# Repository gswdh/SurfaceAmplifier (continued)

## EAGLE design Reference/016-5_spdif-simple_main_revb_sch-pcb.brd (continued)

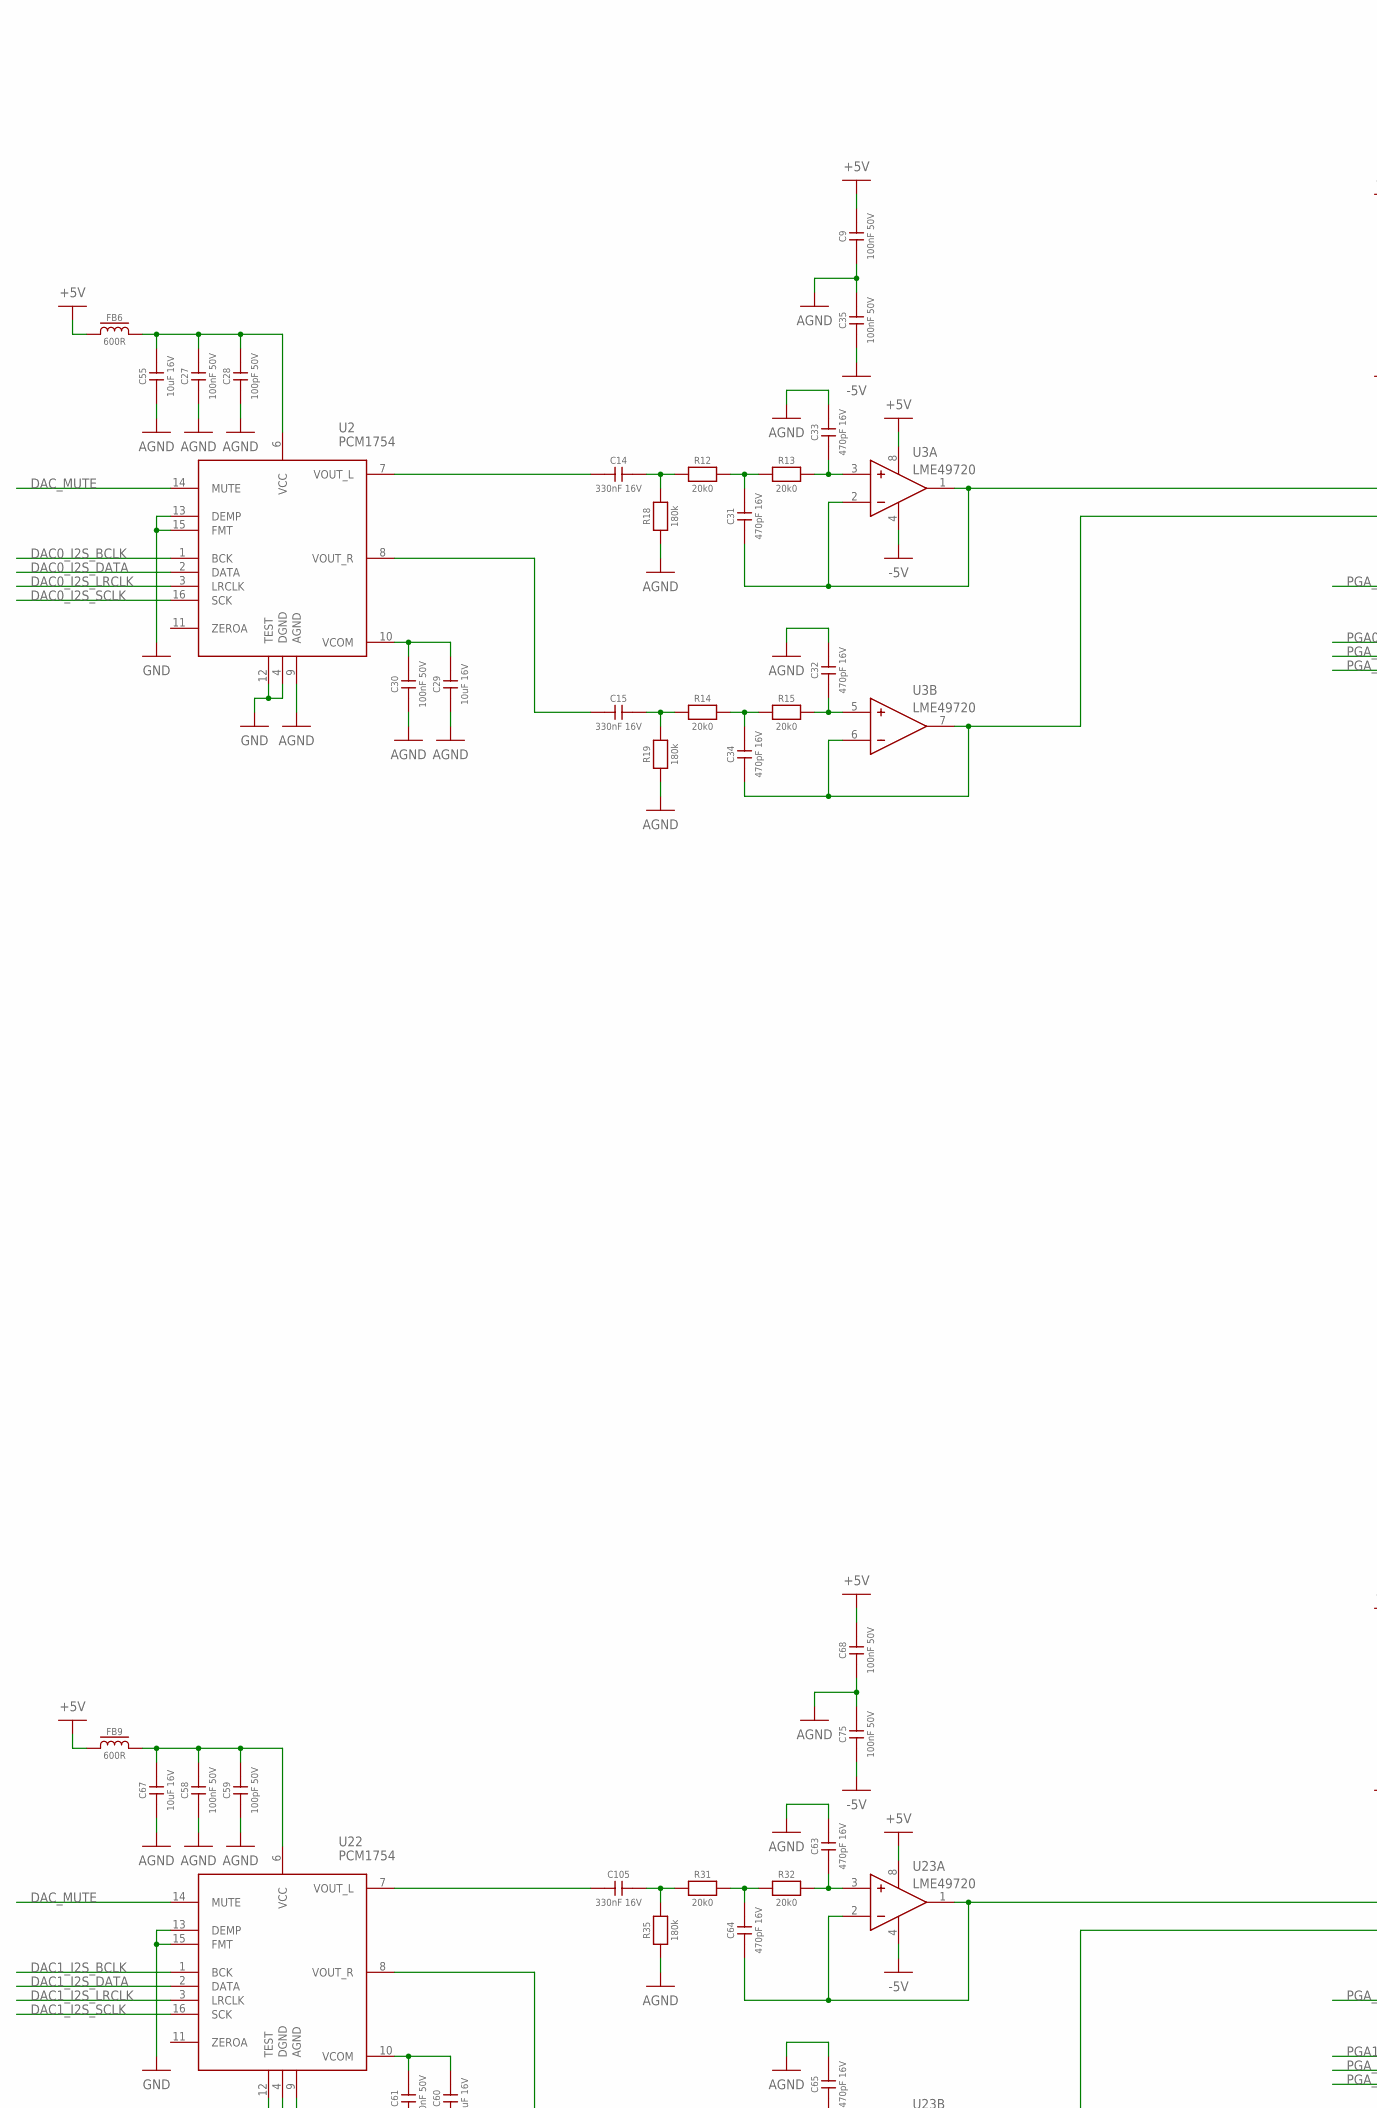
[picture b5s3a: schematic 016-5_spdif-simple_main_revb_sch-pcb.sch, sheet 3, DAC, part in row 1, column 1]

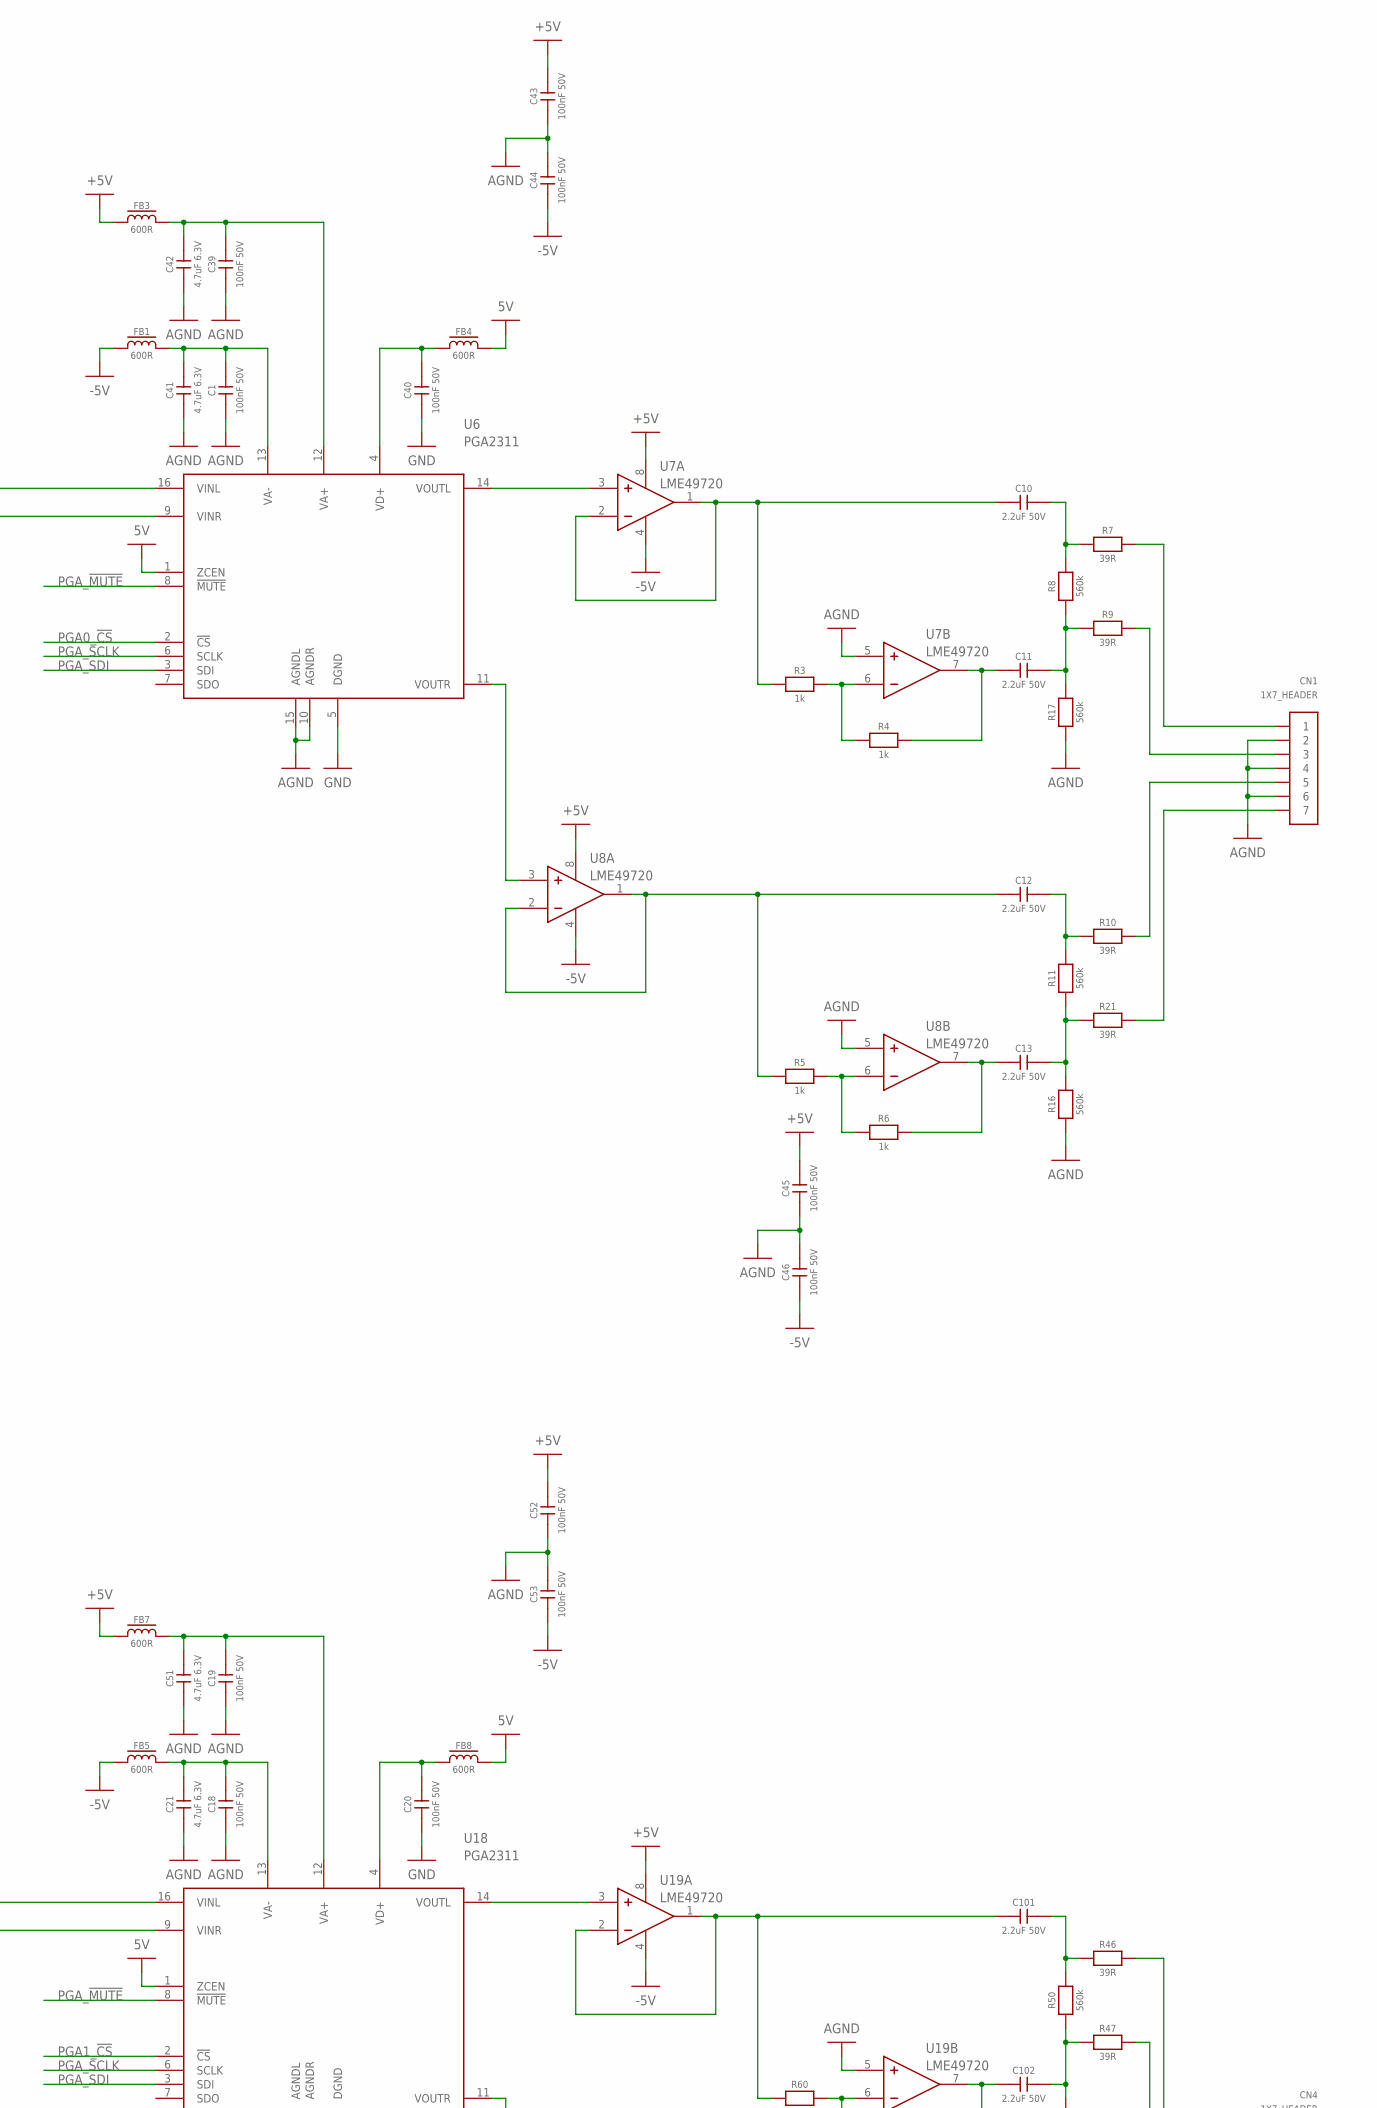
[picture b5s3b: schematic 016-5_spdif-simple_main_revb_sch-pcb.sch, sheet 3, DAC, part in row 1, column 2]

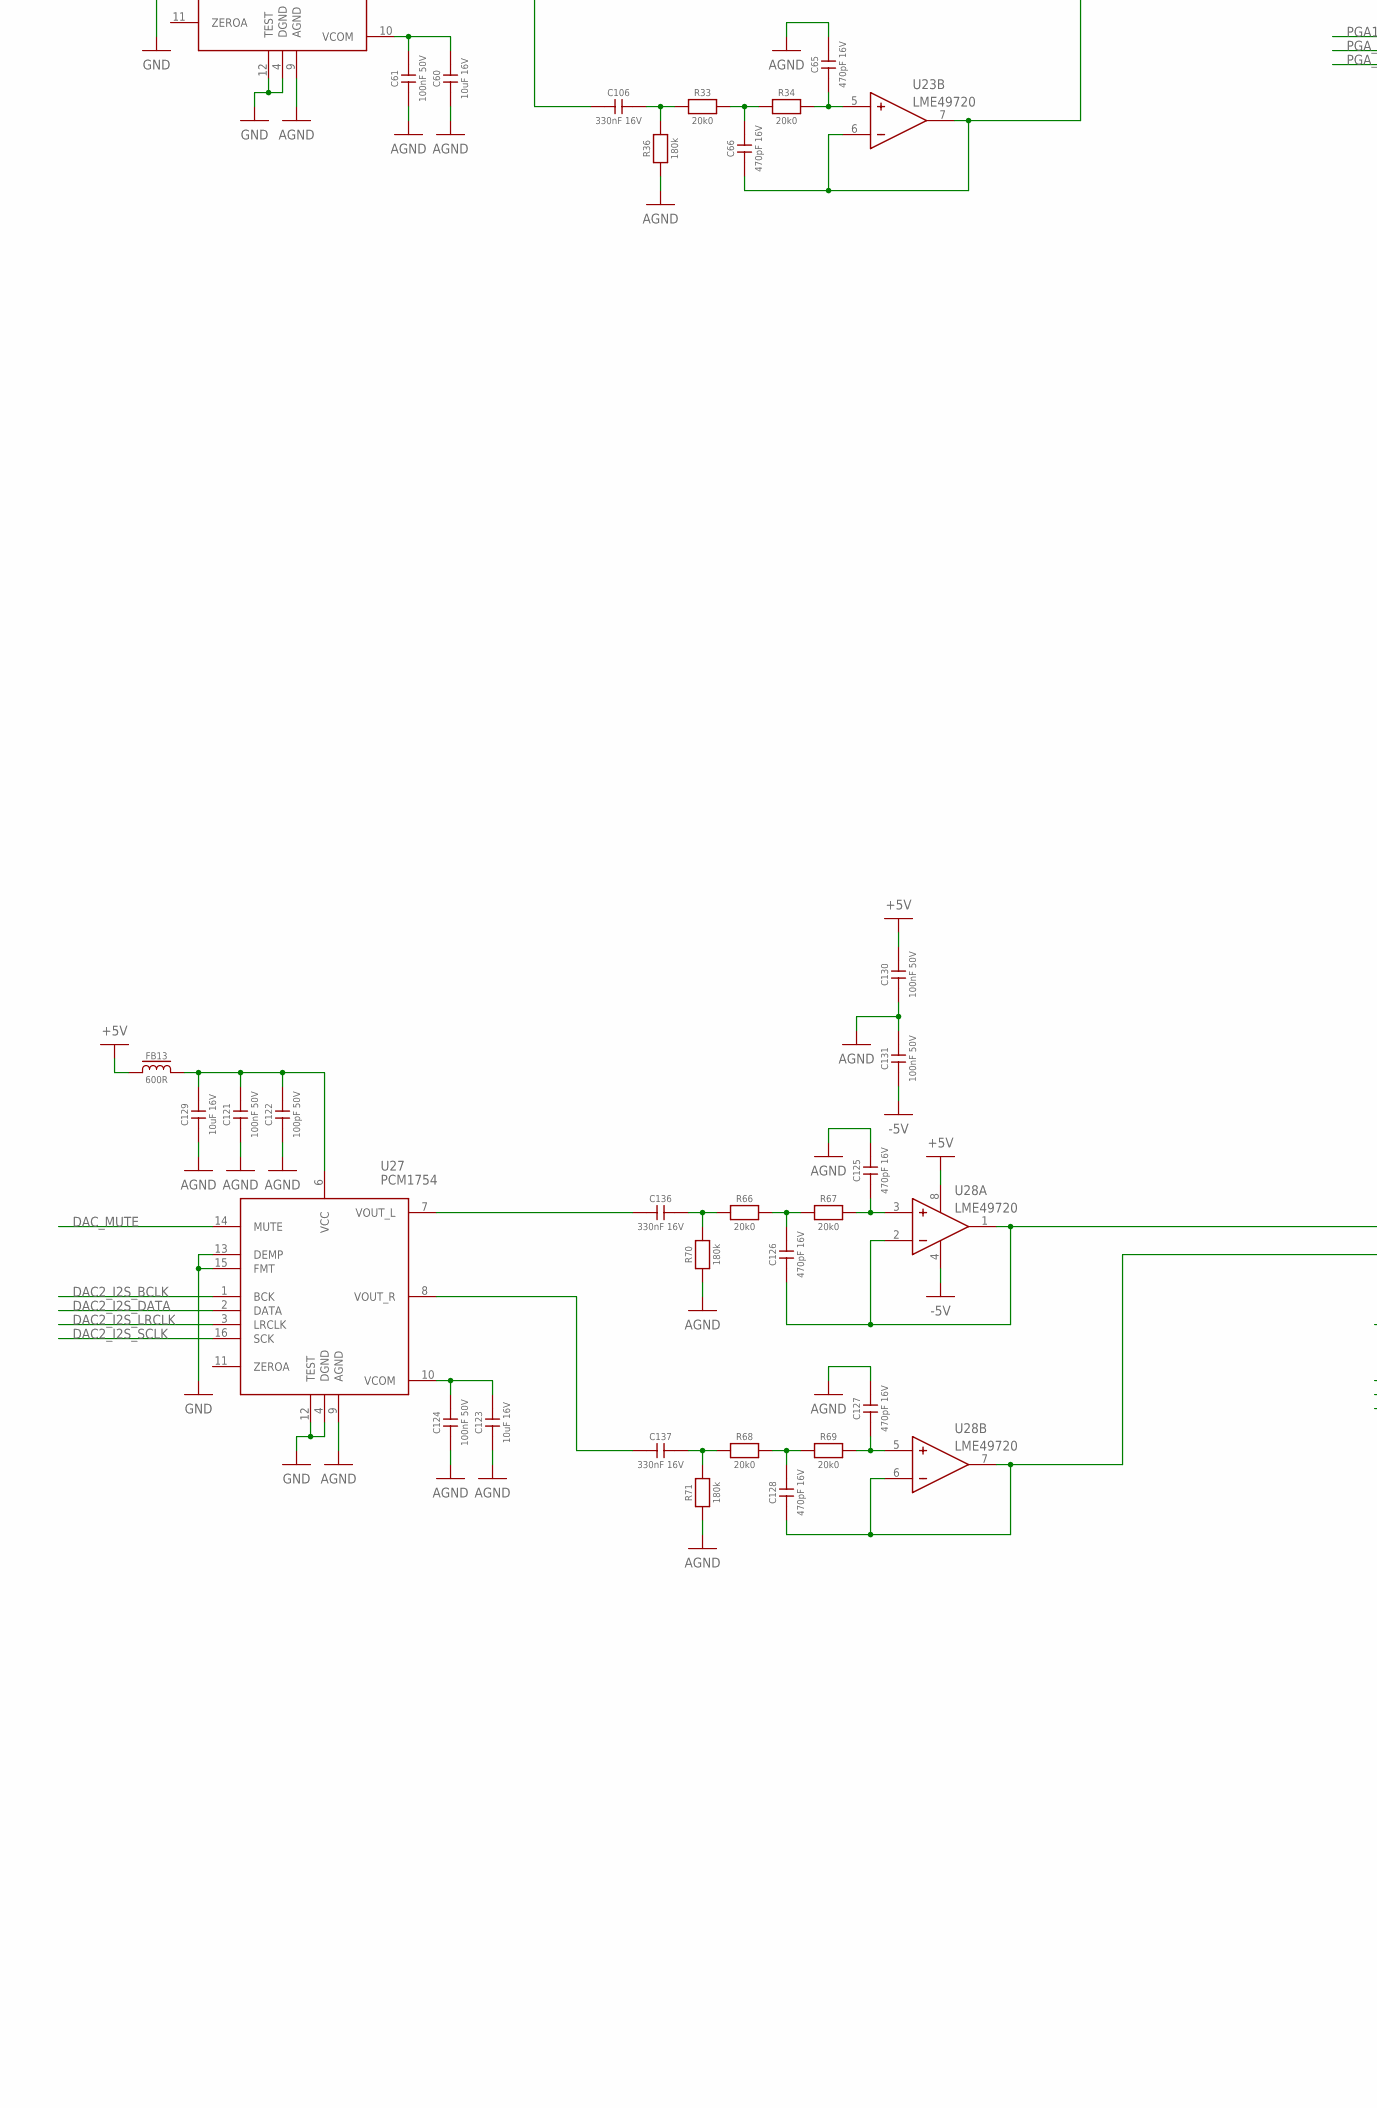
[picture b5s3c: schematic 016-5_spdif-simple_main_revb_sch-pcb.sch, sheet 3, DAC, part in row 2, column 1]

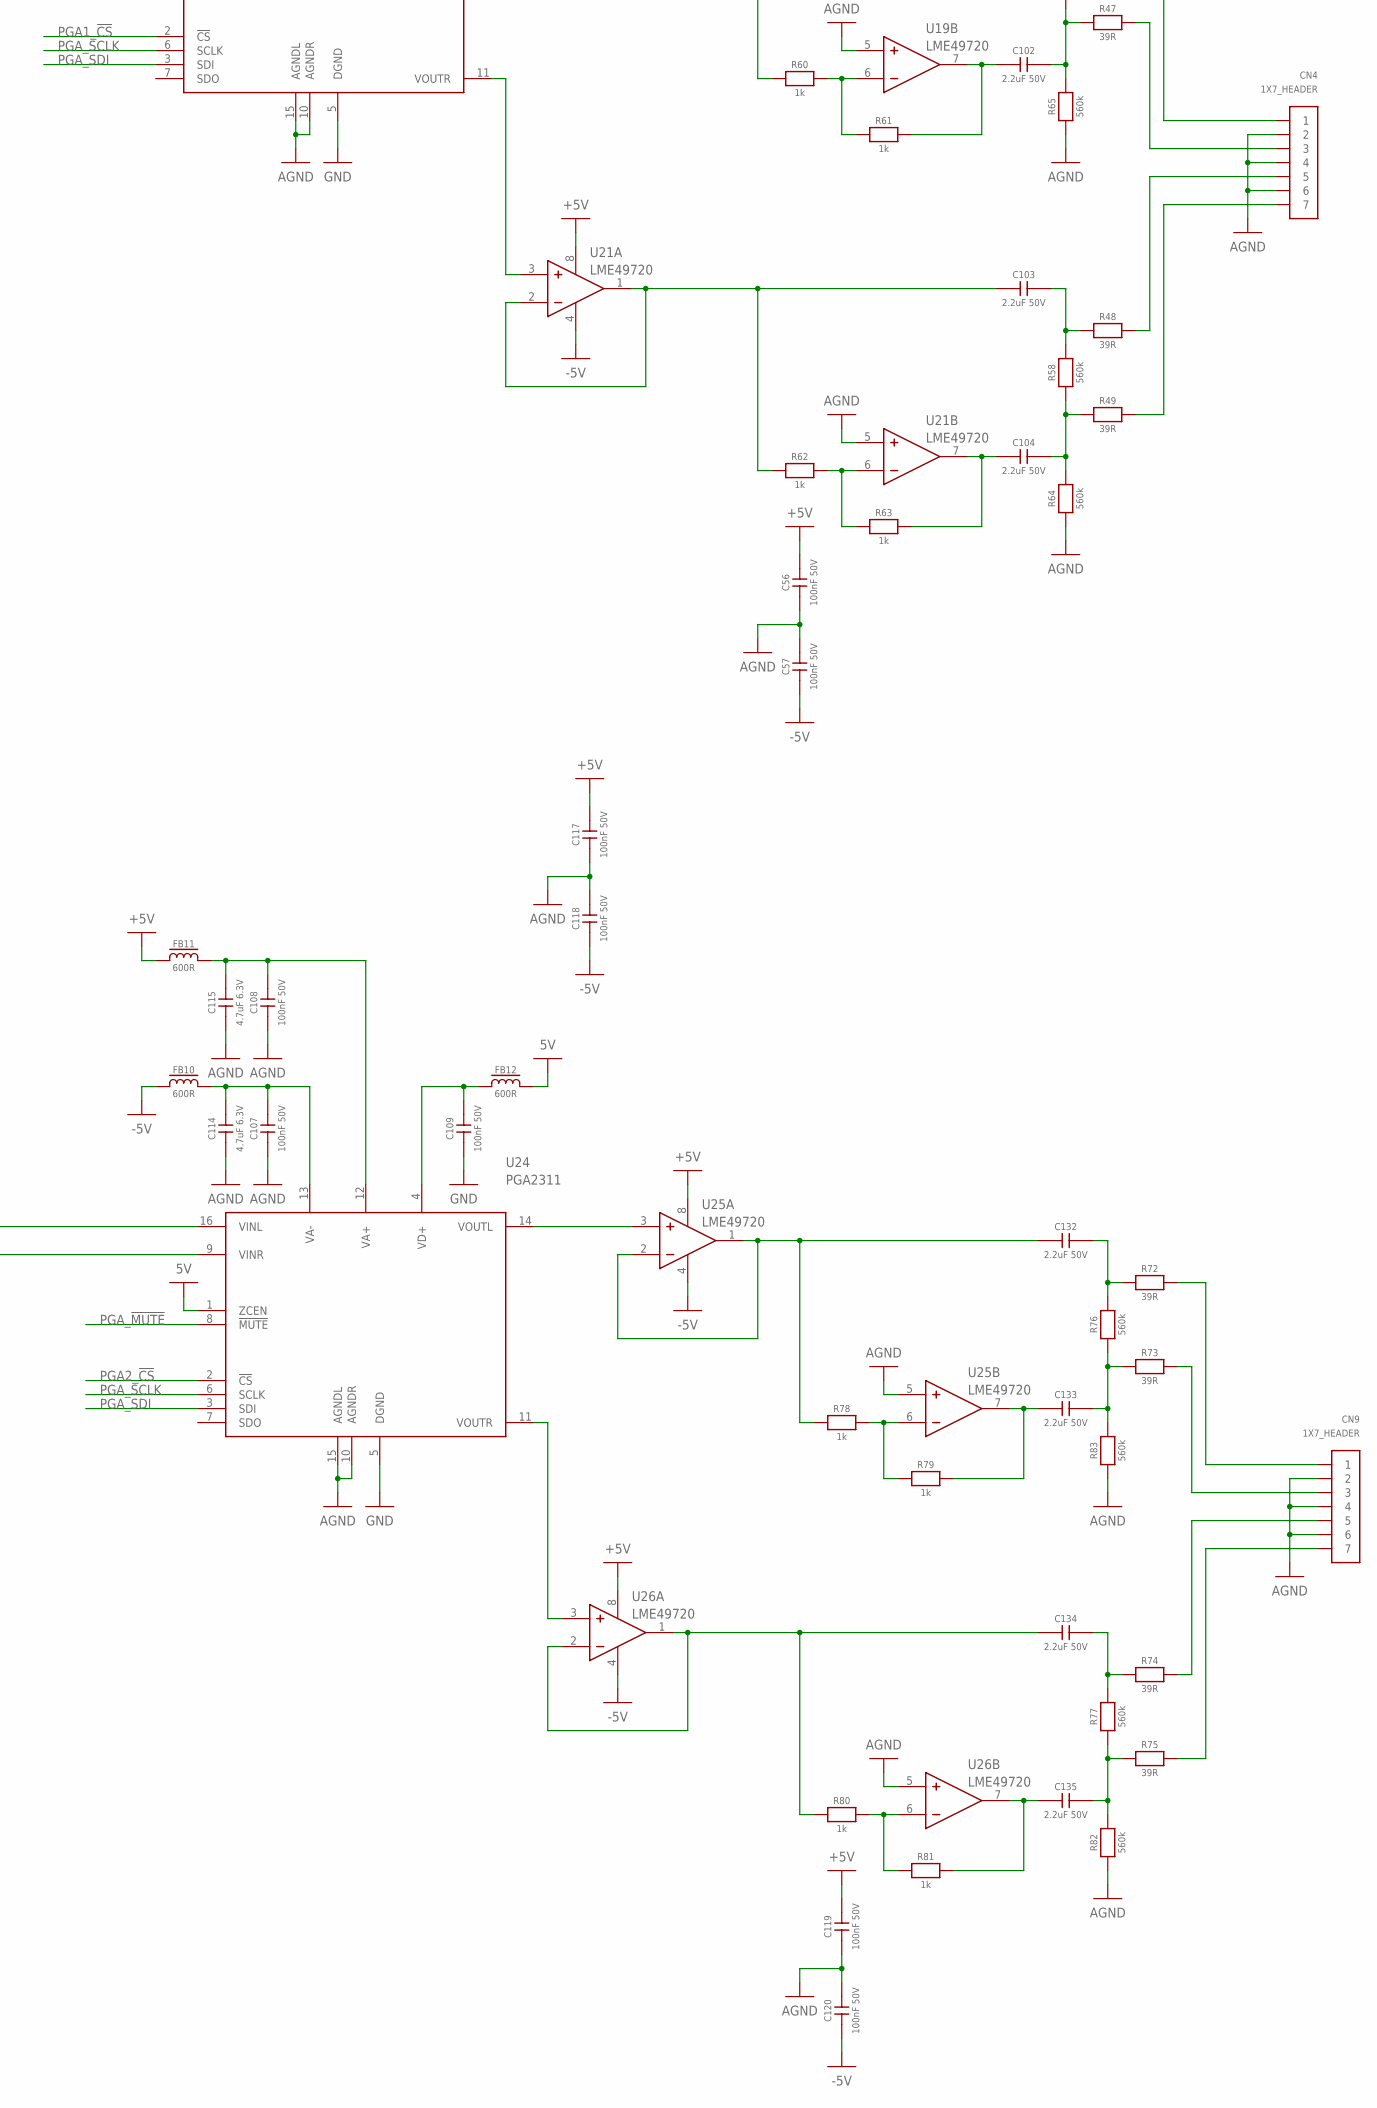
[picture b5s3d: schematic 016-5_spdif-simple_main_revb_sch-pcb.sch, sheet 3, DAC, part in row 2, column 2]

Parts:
C1, C18, C19, C20, C27, C30, C39, C40, C58, C61, C107, C108, C109, C121, C124: 100nF 50V; 0603
C9, C35, C43, C44, C45, C46, C52, C53, C56, C57, C68, C75, C117, C118, C119, C120, C130, C131: 100nF 50V; 0603; FARNELL 2407338
C10, C11, C12, C13, C101, C102, C103, C104, C132, C133, C134, C135: 2.2uF 50V; 5X7.2BOX
C14, C15, C105, C106, C136, C137: 330nF 16V; 1206
C21, C41, C42, C51, C114, C115: 4.7uF 6.3V; 0603
C28, C59, C122: 100pF 50V; 0603
C29, C55, C60, C67, C123, C129: 10uF 16V; 1206
C31, C32, C33, C34, C63, C64, C65, C66, C125, C126, C127, C128: 470pF 16V; 0603
CN1, CN4, CN9: 1X7_HEADER; 7PIN_HEADER
FB1, FB3, FB5, FB6, FB7, FB9, FB10, FB11, FB13: 600R; 0603
FB4, FB8, FB12: 600R; 0603; FARNELL 1635706
R3, R4, R5, R6, R60, R61, R62, R63, R78, R79, R80, R81: 1k; 0603
R7, R9, R10, R21, R46, R47, R48, R49, R72, R73, R74, R75: 39R; 0603
R8, R11, R16, R17, R50, R58, R64, R65, R76, R77, R82, R83: 560k; 0603
R12, R13, R14, R15, R31, R32, R33, R34, R66, R67, R68, R69: 20k0; 0603
R18, R19, R35, R36, R70, R71: 180k; 0603
U2, U22, U27: PCM1754; SSOP16-4MM@1
U3, U7, U8, U19, U21, U23, U25, U26, U28: LME49720; SO8
U6, U18, U24: PGA2311; SOL16

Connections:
5V: FB4.2, FB8.2, FB12.2, U6.1 (ZCEN), U18.1 (ZCEN), U24.1 (ZCEN); also elsewhere on the board
+5V: C9.2, C43.2, C45.2, C52.2, C56.2, C68.2, C117.2, C119.2, C130.2, FB3.1, FB6.2, FB7.1, FB9.2, FB11.1, FB13.2, U3.8 (V+), U7.8 (V+), U8.8 (V+), U19.8 (V+), U21.8 (V+), U23.8 (V+), U25.8 (V+), U26.8 (V+), U28.8 (V+); also elsewhere on the board
-5V: C35.1, C44.1, C46.1, C53.1, C57.1, C75.1, C118.1, C120.1, C131.1, FB1.1, FB5.1, FB10.1, U3.4 (V-), U7.4 (V-), U8.4 (V-), U19.4 (V-), U21.4 (V-), U23.4 (V-), U25.4 (V-), U26.4 (V-), U28.4 (V-); also elsewhere on the board
AGND: C1.1, C9.1, C18.1, C19.1, C21.1, C27.1, C28.1, C29.1, C30.1, C32.2, C33.2, C35.2, C39.1, C41.1, C42.1, C43.1, C44.2, C45.1, C46.2, C51.1, C52.1, C53.2, C55.1, C56.1, C57.2, C58.1, C59.1, C60.1, C61.1, C63.2, C65.2, C67.1, C68.1, C75.2, C107.1, C108.1, C114.1, C115.1, C117.1, C118.2, C119.1, C120.2, C121.1, C122.1, C123.1, C124.1, C125.2, C127.2, C129.1, C130.1, C131.2, CN1.2, CN1.4, CN1.6, CN4.2, CN4.4, CN4.6, CN9.2, CN9.4, CN9.6, R16.1, R17.1, R18.1, R19.1, R35.1, R36.1, R64.1, R65.1, R70.1, R71.1, R82.1, R83.1, U2.9 (AGND), U6.10 (AGNDR), U6.15 (AGNDL), U7.5 (+), U8.5 (+), U18.10 (AGNDR), U18.15 (AGNDL), U19.5 (+), U21.5 (+), U22.9 (AGND), U24.10 (AGNDR), U24.15 (AGNDL), U25.5 (+), U26.5 (+), U27.9 (AGND); also elsewhere on the board
DAC0_I2S_BCLK: U2.1 (BCK); also elsewhere on the board
DAC0_I2S_DATA: U2.2 (DATA); also elsewhere on the board
DAC0_I2S_LRCLK: U2.3 (LRCLK); also elsewhere on the board
DAC0_I2S_SCLK: U2.16 (SCK); also elsewhere on the board
DAC1_I2S_BCLK: U22.1 (BCK); also elsewhere on the board
DAC1_I2S_DATA: U22.2 (DATA); also elsewhere on the board
DAC1_I2S_LRCLK: U22.3 (LRCLK); also elsewhere on the board
DAC1_I2S_SCLK: U22.16 (SCK); also elsewhere on the board
DAC2_I2S_BCLK: U27.1 (BCK); also elsewhere on the board
DAC2_I2S_DATA: U27.2 (DATA); also elsewhere on the board
DAC2_I2S_LRCLK: U27.3 (LRCLK); also elsewhere on the board
DAC2_I2S_SCLK: U27.16 (SCK); also elsewhere on the board
DAC_MUTE: U2.14 (MUTE), U22.14 (MUTE), U27.14 (MUTE); also elsewhere on the board
GND: C20.1, C40.1, C109.1, U2.4 (DGND), U2.12 (TEST), U2.13 (DEMP), U2.15 (FMT), U6.5 (DGND), U18.5 (DGND), U22.4 (DGND), U22.12 (TEST), U22.13 (DEMP), U22.15 (FMT), U24.5 (DGND), U27.4 (DGND), U27.12 (TEST), U27.13 (DEMP), U27.15 (FMT); also elsewhere on the board
unnamed: R5.2, R6.1, U8.6 (-)
unnamed: C13.1, R6.2, U8.7 (OUT)
unnamed: C10.2, R7.1, R8.2
unnamed: C11.2, R8.1, R9.1, R17.2
unnamed: C12.2, R10.1, R11.2
unnamed: C13.2, R11.1, R16.2, R21.1
unnamed: CN1.1, R7.2
unnamed: C27.2, C28.2, C55.2, FB6.1, U2.6 (VCC)
unnamed: C15.2, R14.1, R19.2
unnamed: C14.2, R12.1, R18.2
unnamed: C29.2, C30.2, U2.10 (VCOM)
unnamed: C31.2, R12.2, R13.1
unnamed: C33.1, R13.2, U3.3 (+)
unnamed: C31.1, U3.1 (OUT), U3.2 (-), U6.16 (VINL)
unnamed: C34.2, R14.2, R15.1
unnamed: C32.1, R15.2, U3.5 (+)
unnamed: C34.1, U3.6 (-), U3.7 (OUT), U6.9 (VINR)
unnamed: C15.1, U2.8 (VOUT_R)
unnamed: C14.1, U2.7 (VOUT_L)
unnamed: C1.2, C41.2, FB1.2, U6.13 (VA-)
unnamed: C39.2, C42.2, FB3.2, U6.12 (VA+)
unnamed: C40.2, FB4.1, U6.4 (VD+)
unnamed: C10.1, R3.1, U7.1 (OUT), U7.2 (-)
unnamed: U6.14 (VOUTL), U7.3 (+)
unnamed: R3.2, R4.1, U7.6 (-)
unnamed: CN1.7, R21.2
unnamed: CN1.5, R10.2
unnamed: C12.1, R5.1, U8.1 (OUT), U8.2 (-)
unnamed: U6.11 (VOUTR), U8.3 (+)
unnamed: C18.2, C21.2, FB5.2, U18.13 (VA-)
unnamed: CN1.3, R9.2
unnamed: C11.1, R4.2, U7.7 (OUT)
unnamed: C19.2, C51.2, FB7.2, U18.12 (VA+)
unnamed: C20.2, FB8.1, U18.4 (VD+)
unnamed: C101.1, R60.1, U19.1 (OUT), U19.2 (-)
unnamed: U18.14 (VOUTL), U19.3 (+)
unnamed: R60.2, R61.1, U19.6 (-)
unnamed: C103.1, R62.1, U21.1 (OUT), U21.2 (-)
unnamed: U18.11 (VOUTR), U21.3 (+)
unnamed: R62.2, R63.1, U21.6 (-)
unnamed: C104.1, R63.2, U21.7 (OUT)
unnamed: C58.2, C59.2, C67.2, FB9.1, U22.6 (VCC)
unnamed: C60.2, C61.2, U22.10 (VCOM)
unnamed: C64.2, R31.2, R32.1
unnamed: C63.1, R32.2, U23.3 (+)
unnamed: C64.1, U18.16 (VINL), U23.1 (OUT), U23.2 (-)
unnamed: C66.2, R33.2, R34.1
unnamed: C65.1, R34.2, U23.5 (+)
unnamed: C66.1, U18.9 (VINR), U23.6 (-), U23.7 (OUT)
unnamed: C106.1, U22.8 (VOUT_R)
unnamed: C105.1, U22.7 (VOUT_L)
unnamed: C101.2, R46.1, R50.2
unnamed: C102.2, R47.1, R50.1, R65.2
unnamed: C103.2, R48.1, R58.2
unnamed: C104.2, R49.1, R58.1, R64.2
unnamed: CN4.1, R46.2
unnamed: CN4.5, R48.2
unnamed: C102.1, R61.2, U19.7 (OUT)
unnamed: CN4.7, R49.2
unnamed: CN4.3, R47.2
unnamed: C106.2, R33.1, R36.2
unnamed: C105.2, R31.1, R35.2
unnamed: C107.2, C114.2, FB10.2, U24.13 (VA-)
unnamed: C108.2, C115.2, FB11.2, U24.12 (VA+)
unnamed: C109.2, FB12.1, U24.4 (VD+)
unnamed: C132.1, R78.1, U25.1 (OUT), U25.2 (-)
unnamed: U24.14 (VOUTL), U25.3 (+)
unnamed: R78.2, R79.1, U25.6 (-)
unnamed: C134.1, R80.1, U26.1 (OUT), U26.2 (-)
unnamed: U24.11 (VOUTR), U26.3 (+)
unnamed: R80.2, R81.1, U26.6 (-)
unnamed: C135.1, R81.2, U26.7 (OUT)
unnamed: C121.2, C122.2, C129.2, FB13.1, U27.6 (VCC)
unnamed: C123.2, C124.2, U27.10 (VCOM)
unnamed: C126.2, R66.2, R67.1
unnamed: C125.1, R67.2, U28.3 (+)
unnamed: C126.1, U24.16 (VINL), U28.1 (OUT), U28.2 (-)
unnamed: C128.2, R68.2, R69.1
unnamed: C127.1, R69.2, U28.5 (+)
unnamed: C128.1, U24.9 (VINR), U28.6 (-), U28.7 (OUT)
unnamed: C137.1, U27.8 (VOUT_R)
unnamed: C136.1, U27.7 (VOUT_L)
unnamed: C132.2, R72.1, R76.2
unnamed: C133.2, R73.1, R76.1, R83.2
unnamed: C134.2, R74.1, R77.2
unnamed: C135.2, R75.1, R77.1, R82.2
unnamed: CN9.1, R72.2
unnamed: CN9.5, R74.2
unnamed: C133.1, R79.2, U25.7 (OUT)
unnamed: CN9.7, R75.2
unnamed: CN9.3, R73.2
unnamed: C137.2, R68.1, R71.2
unnamed: C136.2, R66.1, R70.2
PGA0_!CS: U6.2 (!CS); also elsewhere on the board
PGA1_!CS: U18.2 (!CS); also elsewhere on the board
PGA2_!CS: U24.2 (!CS); also elsewhere on the board
PGA_!MUTE: U6.8 (!MUTE), U18.8 (!MUTE), U24.8 (!MUTE); also elsewhere on the board
PGA_SCLK: U6.6 (SCLK), U18.6 (SCLK), U24.6 (SCLK); also elsewhere on the board
PGA_SDI: U6.3 (SDI), U18.3 (SDI), U24.3 (SDI); also elsewhere on the board

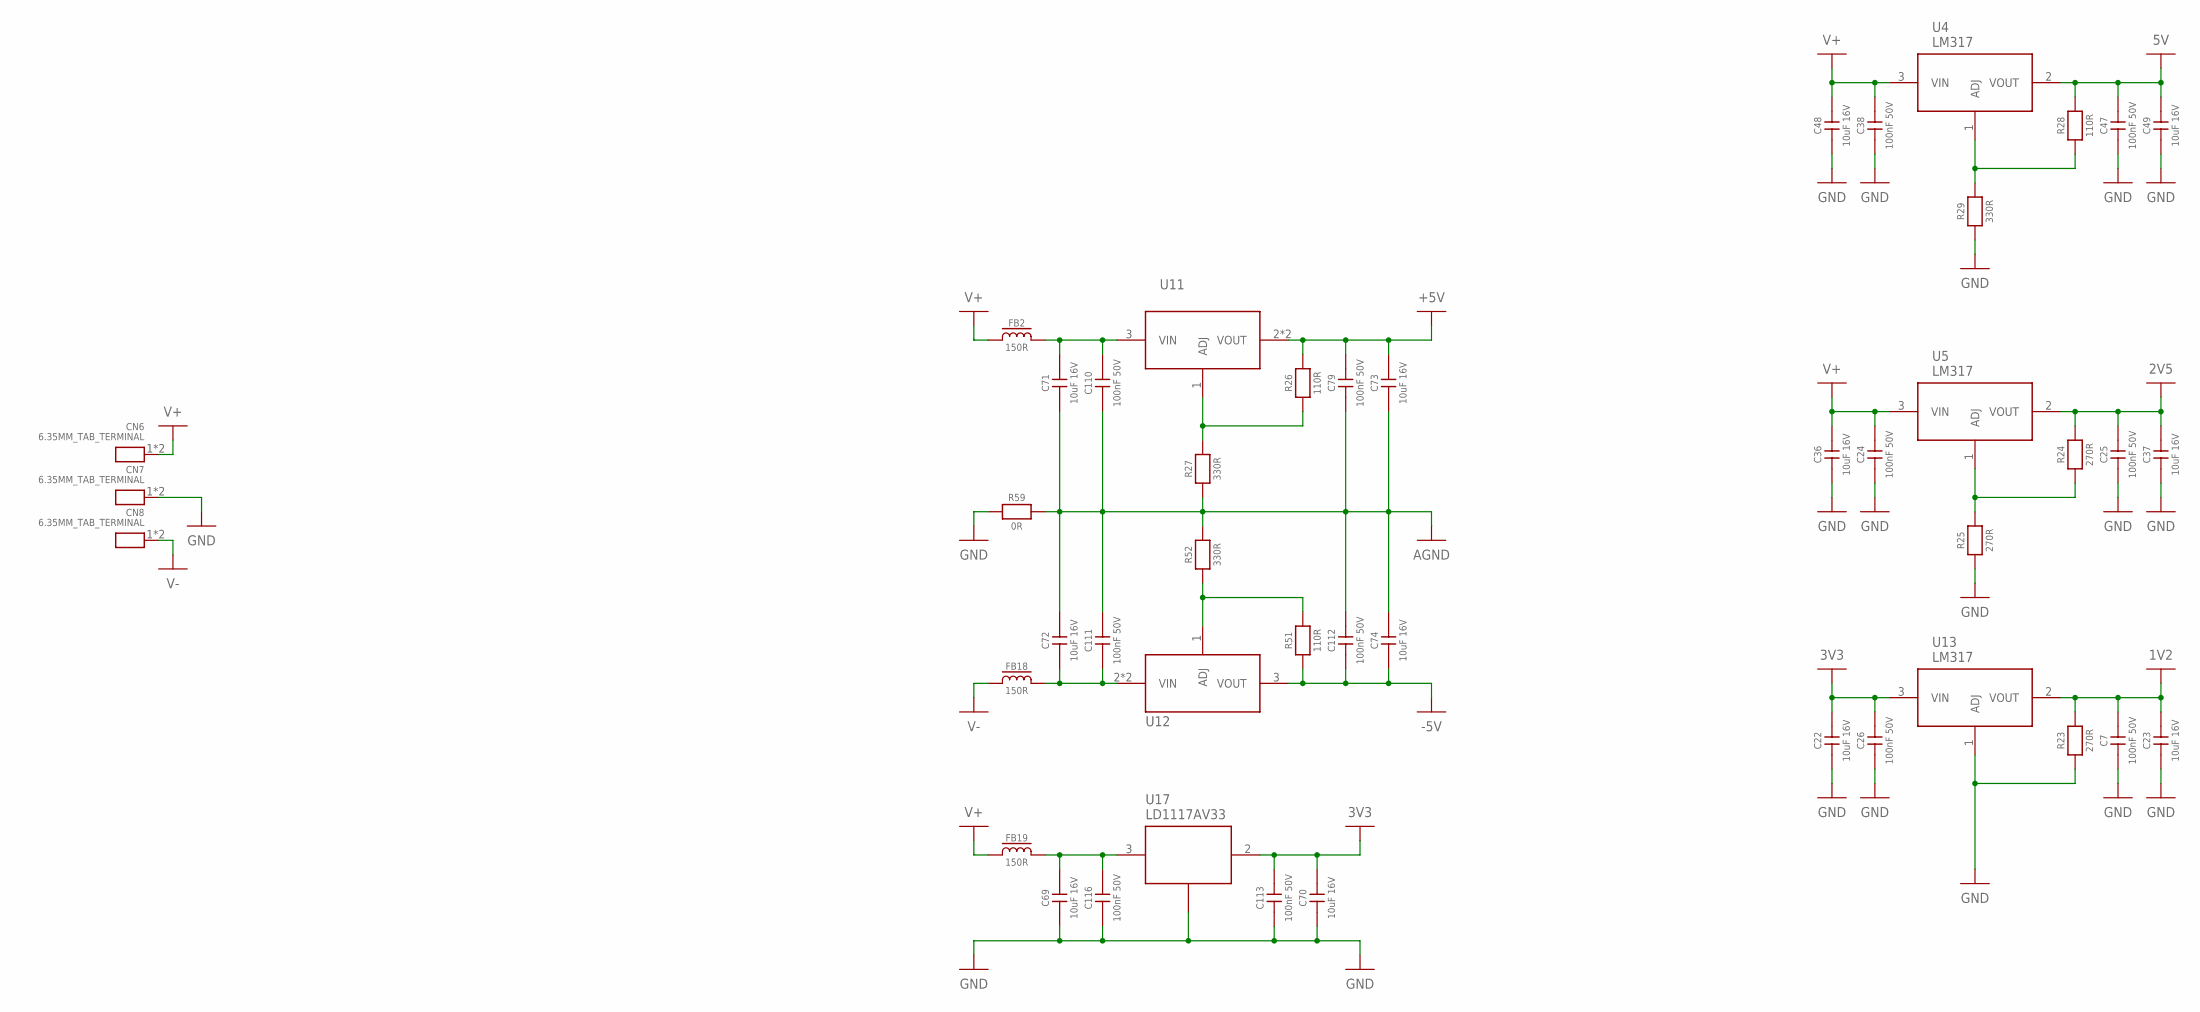
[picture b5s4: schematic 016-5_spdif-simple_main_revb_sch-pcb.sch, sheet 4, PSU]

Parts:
C7, C24, C25, C26, C38, C47: 100nF 50V; 0603; FARNELL 2407338
C22, C23, C36, C37, C48, C49, C69, C70, C71, C72, C73, C74: 10uF 16V; 1206
C79, C110, C111, C112, C113, C116: 100nF 50V; 0603
CN6, CN7, CN8: 6.35MM_TAB_TERMINAL; 6.35MM_TERMINAL
FB2, FB18, FB19: 150R; 1206
R23, R24, R25: 270R; 0603
R26, R28, R51: 110R; 0603
R27, R29, R52: 330R; 0603
R59: 0R; 0603
U4, U5, U13: LM317; SOT89
U11: LM317MQDCYR; SOT223
U12: LM337IMP; SOT223
U17: LD1117AV33; TO220

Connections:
1V2: C7.2, C23.2, R23.2, U13.2 (VOUT); also elsewhere on the board
2V5: C25.2, C37.2, R24.2, U5.2 (VOUT); also elsewhere on the board
3V3: C22.2, C26.2, C70.2, C113.2, U13.3 (VIN), U17.2 (VOUT); also elsewhere on the board
5V: C47.2, C49.2, R28.2, U4.2 (VOUT); also elsewhere on the board
+5V: C73.2, C79.2, R26.2, U11.2 (VOUT), U11.4 (VOUT); also elsewhere on the board
-5V: C74.1, C112.1, R51.1, U12.3 (VOUT); also elsewhere on the board
AGND: C71.1, C72.2, C73.1, C74.2, C79.1, C110.1, C111.2, C112.2, R27.1, R52.2, R59.2; also elsewhere on the board
GND: C7.1, C22.1, C23.1, C24.1, C25.1, C26.1, C36.1, C37.1, C38.1, C47.1, C48.1, C49.1, C69.1, C70.1, C113.1, C116.1, CN7.1, CN7.2, R23.1, R25.1, R29.1, R59.1, U13.1 (ADJ), U17.1 (GND); also elsewhere on the board
unnamed: R24.1, R25.2, U5.1 (ADJ)
unnamed: R26.1, R27.2, U11.1 (ADJ)
unnamed: C69.2, C116.2, FB19.2, U17.3 (VIN)
unnamed: R28.1, R29.2, U4.1 (ADJ)
unnamed: R51.2, R52.1, U12.1 (ADJ)
unnamed: C72.1, C111.1, FB18.2, U12.2 (VIN), U12.4 (VIN)
unnamed: C71.2, C110.2, FB2.2, U11.3 (VIN)
V+: C24.2, C36.2, C38.2, C48.2, CN6.1, CN6.2, FB2.1, FB19.1, U4.3 (VIN), U5.3 (VIN); also elsewhere on the board
V-: CN8.1, CN8.2, FB18.1

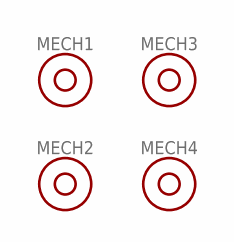
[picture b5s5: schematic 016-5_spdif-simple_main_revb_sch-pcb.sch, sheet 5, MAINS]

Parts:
MECH1, MECH2, MECH3, MECH4: 6mm x 3mm; MOUNTHOLE_6X3
